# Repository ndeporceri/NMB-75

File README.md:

# NMB-75
 Through Hole 75% Keyboard PCB

[BOM](https://octopart.com/bom-tool/1Q1lCkmy "Octopart BOM")

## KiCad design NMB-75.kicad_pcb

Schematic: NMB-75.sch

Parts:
C1, C2: 22pF; C_0805_2012Metric
C3: 1uF; C_0805_2012Metric
C4, C5, C6: .1uF; C_0805_2012Metric
C7: 10uF; C_0805_2012Metric
D1, D2, D3, D4: D_Small; D_SOD-123
F1: 500mA; Fuse_1206_3216Metric
MX1, MX2, MX3, MX4: MX-NoLED; MX-1U-NoLED
R1, R4: 10k; R_1206_3216Metric
R2, R3: 22; R_1206_3216Metric
SW1: SW_Push; SKQG-1155865
U1: ATmega32U4-AU; TQFP-44_10x10mm_P0.8mm
USB1: Molex-0548190589
Y1: 16MHz; Crystal_SMD_3225-4Pin_3.2x2.5mm

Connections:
+5V: C4.1, C5.1, C6.1, C7.1, F1.1, R1.1, U1.2, U1.7, U1.14, U1.24, U1.34, U1.44
COL0: MX1.1, MX3.1, U1.29
COL1: MX2.1, MX4.1, U1.28
D+: R2.2, USB1.3
D-: R3.2, USB1.4
GND: C1.2, C2.2, C3.2, C4.2, C5.2, C6.2, C7.2, R4.1, SW1.1, U1.5, U1.15, U1.23, U1.35, U1.43, USB1.1, Y1.1, Y1.3
unnamed: C1.1, U1.17, Y1.4
unnamed: C2.1, U1.16, Y1.2
unnamed: C3.1, U1.6
unnamed: D1.2, MX1.2
unnamed: D2.2, MX2.2
unnamed: D3.2, MX3.2
unnamed: D4.2, MX4.2
unnamed: R1.2, SW1.2, U1.13
unnamed: R2.1, U1.4
unnamed: R3.1, U1.3
unnamed: R4.2, U1.33
ROW0: D1.1, D2.1, U1.27
ROW1: D3.1, D4.1, U1.30
VCC: F1.2, USB1.5

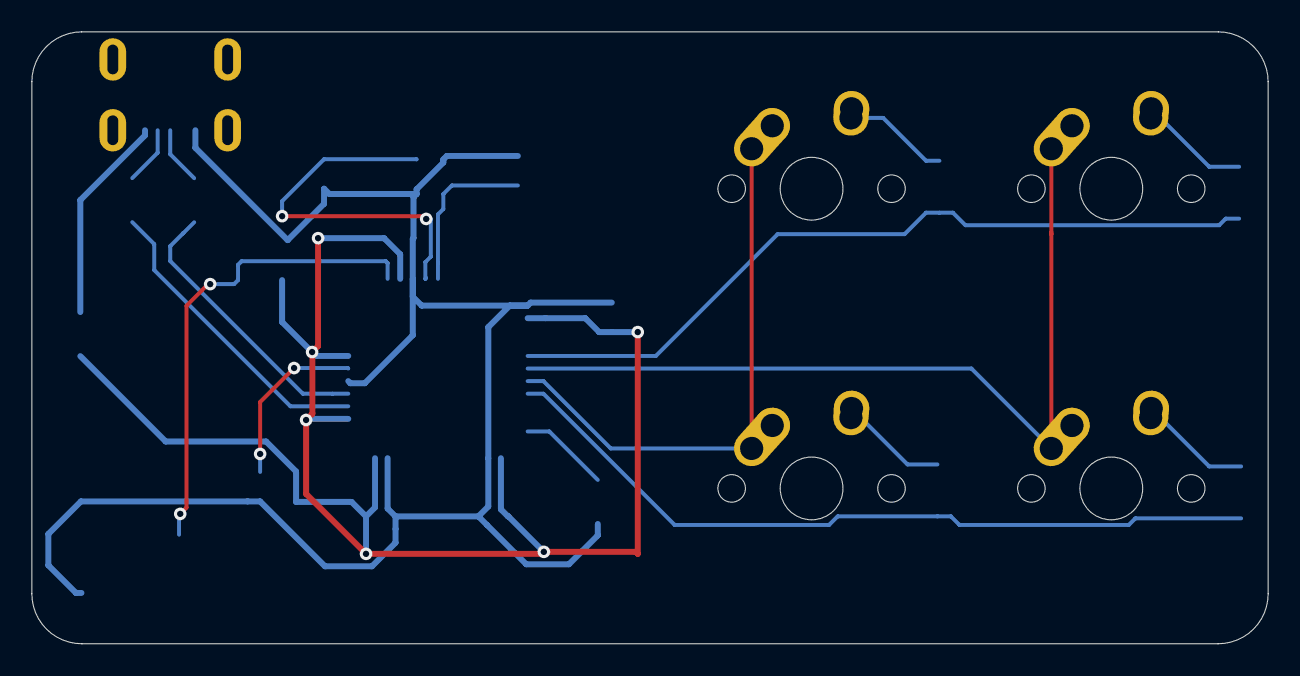
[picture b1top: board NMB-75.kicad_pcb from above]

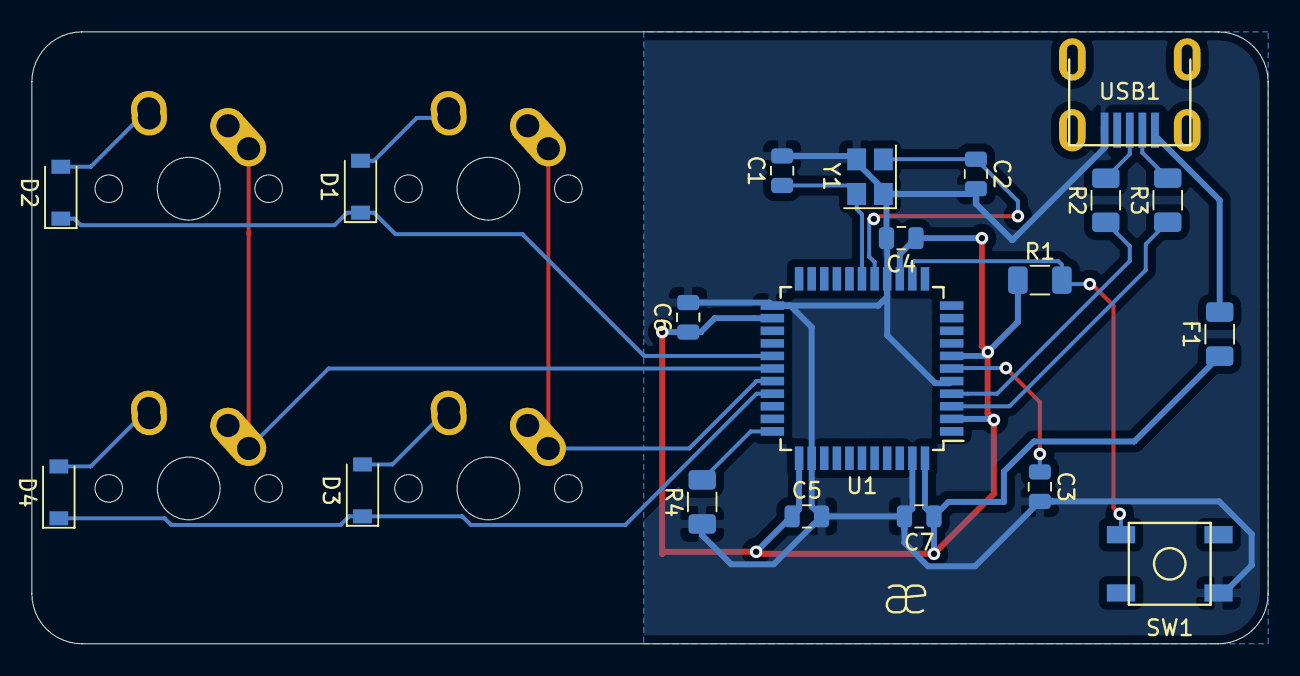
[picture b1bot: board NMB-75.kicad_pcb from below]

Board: 2 copper layers, 78.6 x 38.9 mm, 24 parts (20 on the bottom side), 20 nets.

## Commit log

2021-03-02 KiCad project creation
2021-03-02 Added KiCad libraries
2021-03-02 4x4 schematic
2021-03-02 footprints assigned
2021-03-02 pcb sketch done
2021-03-02 working on traces
2021-03-02 routing finished on learning board
2021-03-02 Added ground fill, decor text and generated gerbers
2021-03-02 Archived learning board locally, deleted unarchived files
2021-03-02 schematic progress
    mcu, isp pins, usb c, buttons, and led laid out
2021-03-02 schematic work
    placed down switches for matrix
2021-03-02 changed matrix staggering
2021-03-03 Footprint assignment progress
    added some footprint libraries, assigned some foot prints.
2021-03-03 added bom to readme
